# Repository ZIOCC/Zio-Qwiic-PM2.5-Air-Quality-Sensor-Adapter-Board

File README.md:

# Zio Qwiic PM2.5 Air Quality Sensor Adapter Board

> This product can be available for purchase [here](https://www.smart-prototyping.com/Zio-Qwiic-PM-Air-Quality-Sensor-and-Adapter-Board).

#### Description

This is a PM sensor + Qwiic adapter board product, you will get the PM sensor and an easy to use adapter board.

The PM sensor is a compact (compare to the other PM sensors) and accurate sensor. It can directly output the PM 1.0, 2.5, 10.0 rate of the air in unit of the µg/m3 (PM standard unit), just like the weather report.

This is an I2C version of the sensor, which also has UART interface version.  The adapter board can be directly attached to the sensor with the female header, and we offer you two ways to setup the connection, the easiest way is to use Qwiic cable to connect to Qwiic connector, with no soldering; another way is soldering the breakout pins. 

The adapter board can be fixed very well by the 2.0mm screws with the two 2.0mm holes on the board. And there are two 3mm mounting holes for you to fix this module to any other place you want.

Note 1: the fan on the sensor needs 5v to drive it. We have added a voltage step-up circuit to convert the I2C 3.3V (Qwiic connector) to 5V for the fan. So please be sure to use 5V power when you are using these breakout pins.

Note 2: The sensor needs to take around 30s to warm up to get the accurate data.

#### Specification

* IC: PMSA003I
* I2C address: 0x12
* Operation Current: less than 100mA
* Operation Temperature: -10 to 60 degrees Celsius.
* Adapter board dimension: 44.3 x 35.0mm
* PM sensor Dimension: 12.2 x 35.3 x 38.3 mm
* Total Weight: 24.8g

#### Links

* [PCB Source file](https://github.com/ZIOCC/Zio-Qwiic-PM2.5-Air-Quality-Sensor-Adapter-Board/tree/master/EAGLE)
* [PCB schematic](https://github.com/ZIOCC/Zio-Qwiic-PM2.5-Air-Quality-Sensor-Adapter-Board/blob/master/zio%20qwiic%20pm%20sensor%20adapter%20board.pdf)
* [Demo code](https://github.com/ZIOCC/Zio-Qwiic-PM2.5-Air-Quality-Sensor-Adapter-Board/tree/master/PMSA003I)
* [PM sensor PMSA003I Datasheet](https://github.com/ZIOCC/Zio-Qwiic-PM2.5-Air-Quality-Sensor-Adapter-Board/blob/master/PMSA003%20series%20data%20manua_English_V2.6.pdf) (Not very good English in the datasheet, [contact us](mailto:info@smart-prototyping.com) if you have any question)

###### About Zio
> Zio is a new line of open sourced, compact, and grid layout boards, fully integrated for Arduino and Qwiic ecosystem. Designed ideally for wearables, robotics, small-space limitations or other on the go projects. Check out other awesome Zio products [here](https://www.smart-prototyping.com/Zio).

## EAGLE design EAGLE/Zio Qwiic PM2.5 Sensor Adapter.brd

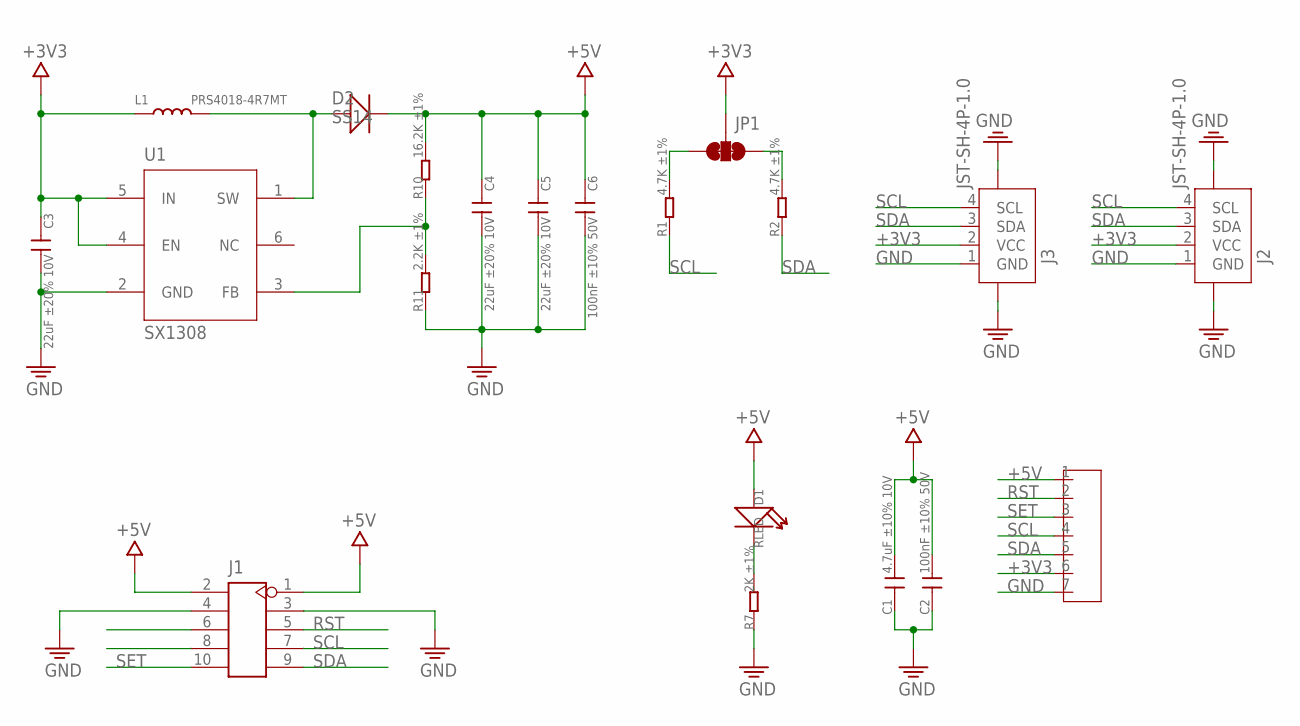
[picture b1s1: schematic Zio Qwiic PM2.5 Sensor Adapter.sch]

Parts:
C1: 4.7uF ±10% 10V; C0603
C2, C6: 100nF ±10% 50V; C0603
C3, C4, C5: 22uF ±20% 10V; C0805
D1: RLED; LED-0603
D2: SS14; DO-214AC
J1: HEADER-2X5P-PM2.5; 2X5P-1.27-THT-PM2.5
J2, J3: JST-SH-4P-1.0; JST-SH-4P
J5: HEADER-7P; 7P-2.54-60/35MIL
JP1: SMT-JUMPER_3_2-NC_TRACE
L1: PRS4018-4R7MT; L4030
R1, R2: 4.7K ±1%; R0603
R7: 2K ±1%; 0603
R10: 16.2K ±1%; R0603
R11: 2.2K ±1%; R0603
U1: SX1308; SOT23-6

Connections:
+3V3: C3.1, J2.2 (VCC), J3.2 (VCC), J5.6, JP1.2, L1.1, U1.4 (EN), U1.5 (IN)
+5V: C1.2, C2.2, C4.1, C5.1, C6.1, D1.+, D2.C (-), J1.1, J1.2, J5.1, R10.2
GND: C1.1, C2.1, C3.2, C4.2, C5.2, C6.2, J1.3, J1.4, J2.1 (GND), J2.NC1 (5), J2.NC2 (6), J3.1 (GND), J3.NC1 (5), J3.NC2 (6), J5.7, R7.1, R11.1, U1.2 (GND)
unnamed: JP1.1, R2.2
unnamed: D1.-, R7.2
unnamed: JP1.3, R1.2
unnamed: R10.1, R11.2, U1.3 (FB)
NC1: J1.6
NC2: J1.8
RST: J1.5, J5.2
SCL: J1.7, J2.4 (SCL), J3.4 (SCL), J5.4, R1.1
SDA: J1.9, J2.3 (SDA), J3.3 (SDA), J5.5, R2.1
SET: J1.10, J5.3
SW: D2.A (+), L1.2, U1.1 (SW)

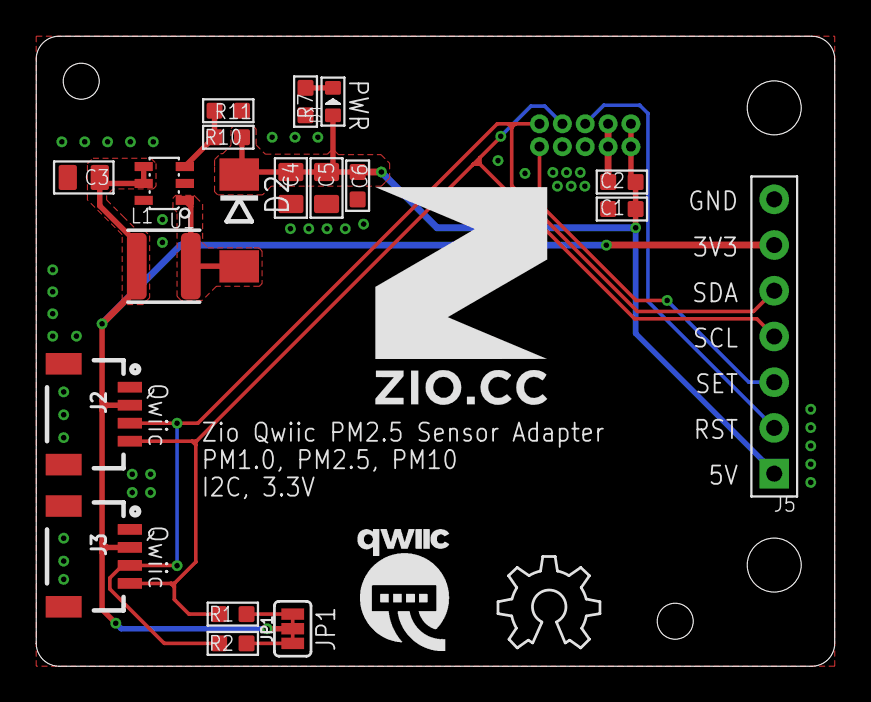
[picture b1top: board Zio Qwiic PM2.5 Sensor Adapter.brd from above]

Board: 2 copper layers, 44.4 x 35.0 mm, 23 parts (1 on the bottom side), 12 nets.

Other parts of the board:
U$6: QWIIC-LOGO-MEDIUM
U$7: OSHW_6X200_NOTEXT
U$9: 12MM
